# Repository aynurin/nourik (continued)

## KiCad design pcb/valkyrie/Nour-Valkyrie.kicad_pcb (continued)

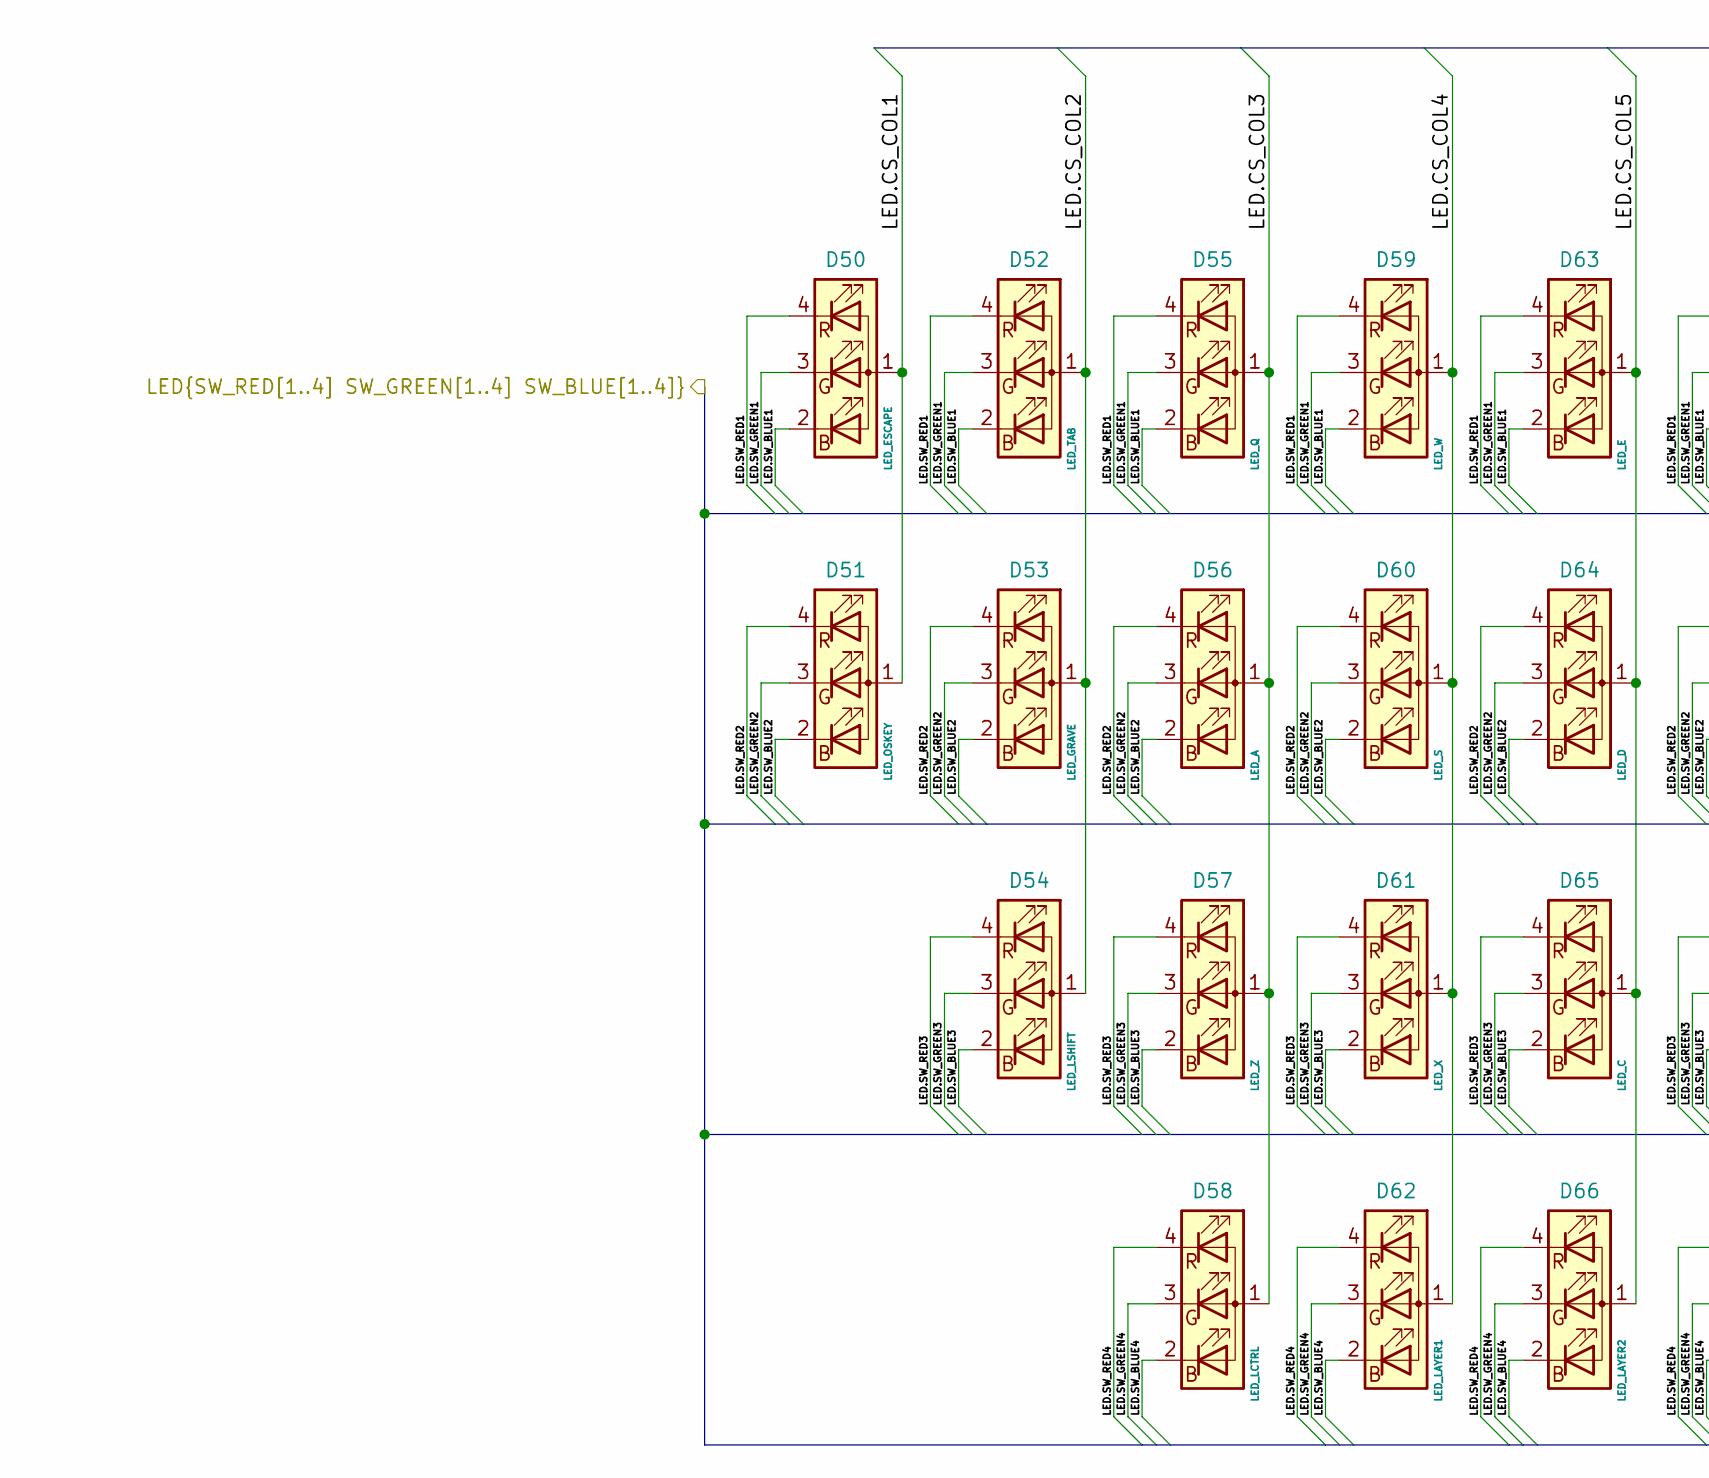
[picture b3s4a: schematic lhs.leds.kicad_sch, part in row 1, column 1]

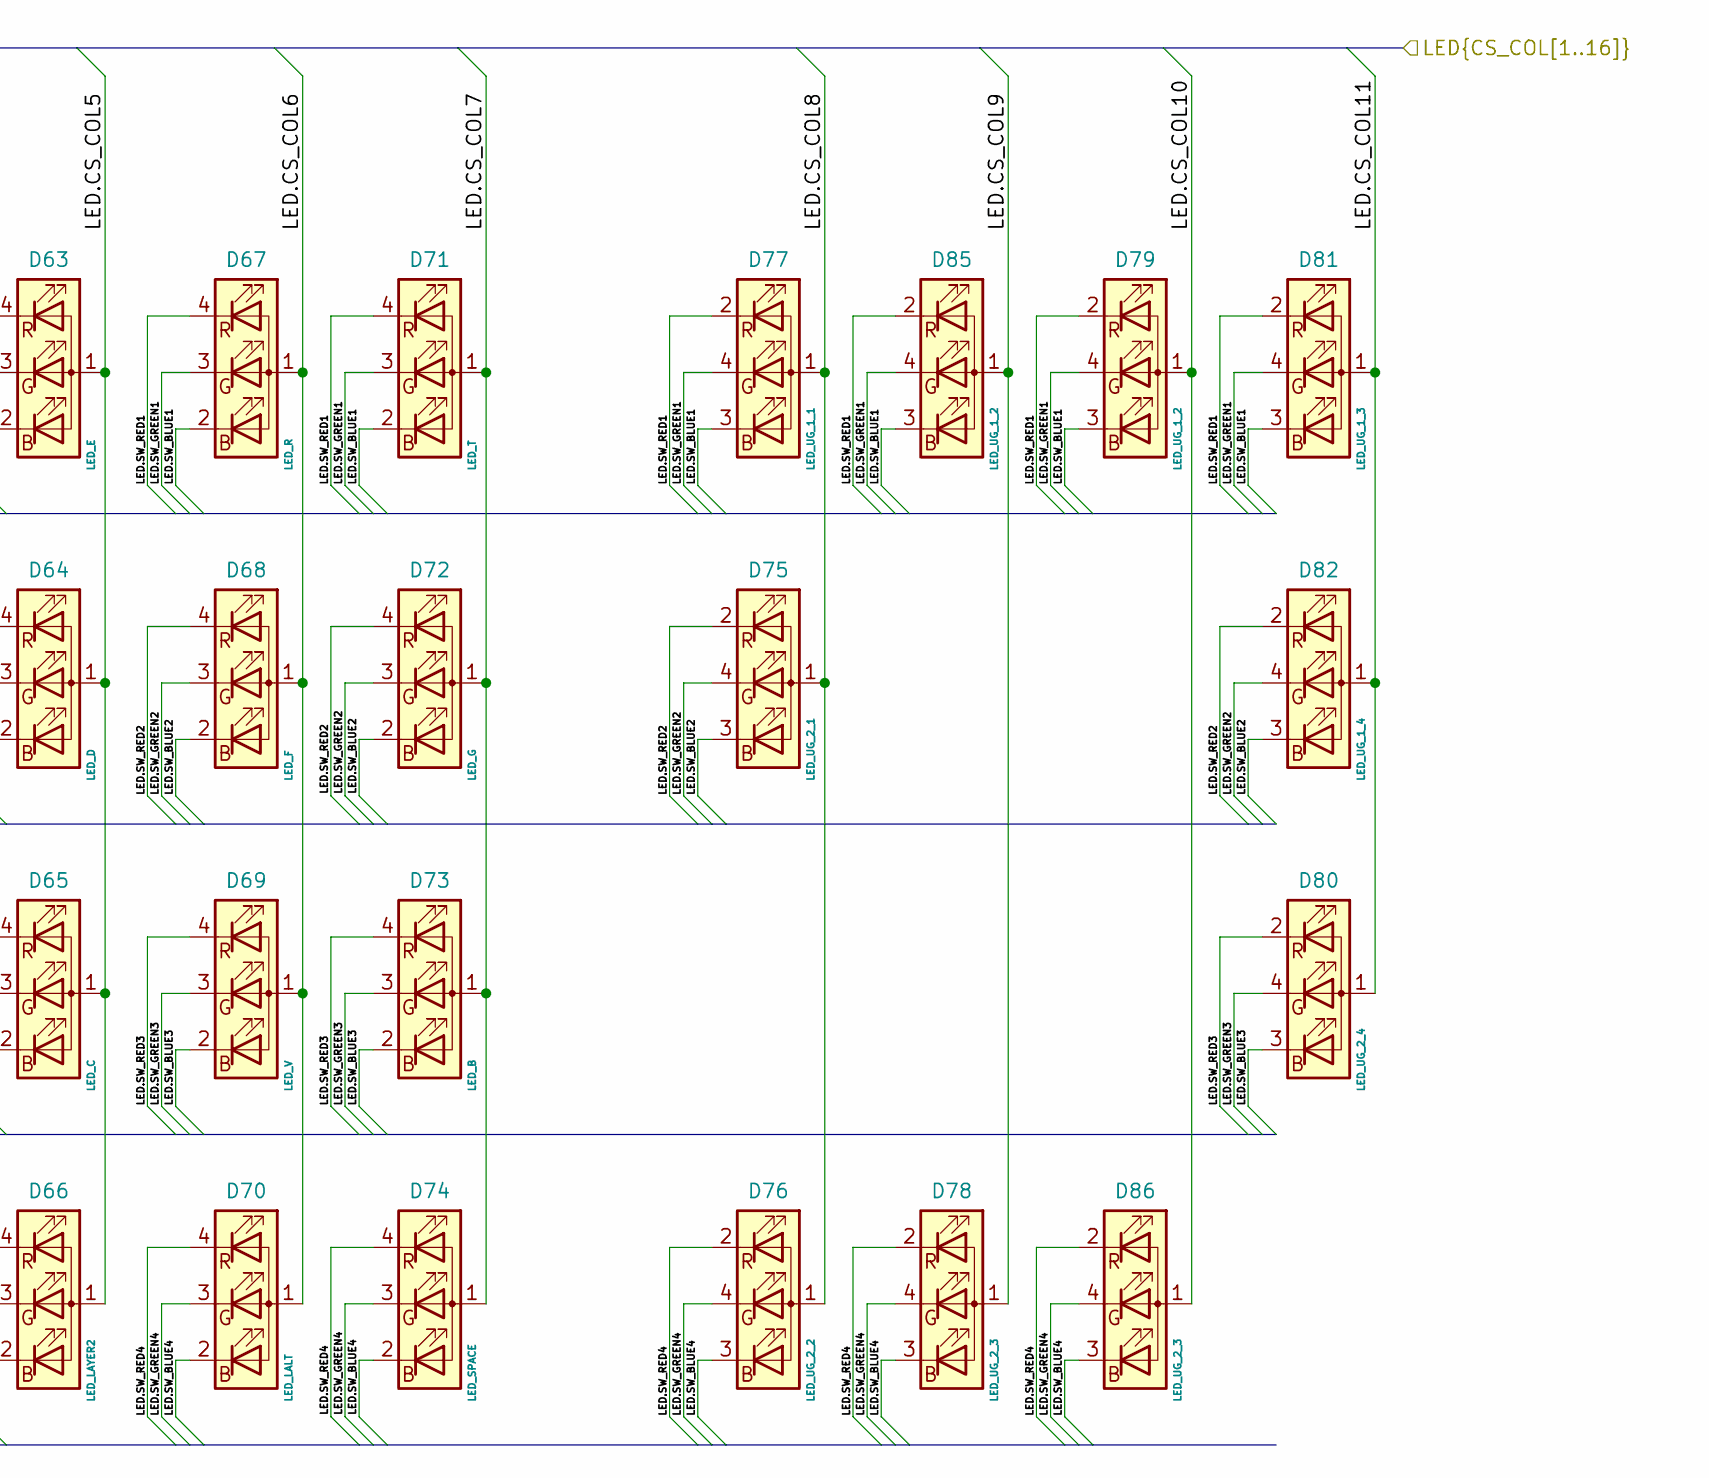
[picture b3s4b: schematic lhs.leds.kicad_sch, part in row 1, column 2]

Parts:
D50: LED_ESCAPE; 155124M173200
D51: LED_OSKEY; 155124M173200
D52: LED_TAB; 155124M173200
D53: LED_GRAVE; 155124M173200
D54: LED_LSHIFT; 155124M173200
D55: LED_Q; 155124M173200
D56: LED_A; 155124M173200
D57: LED_Z; 155124M173200
D58: LED_LCTRL; 155124M173200
D59: LED_W; 155124M173200
D60: LED_S; 155124M173200
D61: LED_X; 155124M173200
D62: LED_LAYER1; 155124M173200
D63: LED_E; 155124M173200
D64: LED_D; 155124M173200
D65: LED_C; 155124M173200
D66: LED_LAYER2; 155124M173200
D67: LED_R; 155124M173200
D68: LED_F; 155124M173200
D69: LED_V; 155124M173200
D70: LED_LALT; 155124M173200
D71: LED_T; 155124M173200
D72: LED_G; 155124M173200
D73: LED_B; 155124M173200
D74: LED_SPACE; 155124M173200
D75: LED_UG_2_1; LTRBR37G4R4S012502R18
D76: LED_UG_2_2; LTRBR37G4R4S012502R18
D77: LED_UG_1_1; LTRBR37G4R4S012502R18
D78, D86: LED_UG_2_3; LTRBR37G4R4S012502R18
D79, D85: LED_UG_1_2; LTRBR37G4R4S012502R18
D80: LED_UG_2_4; LTRBR37G4R4S012502R18
D81: LED_UG_1_3; LTRBR37G4R4S012502R18
D82: LED_UG_1_4; LTRBR37G4R4S012502R18

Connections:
/lhs/LHS LEDs/LED.CS_COL1: D50.1 (A), D51.1 (A); also elsewhere on the board
/lhs/LHS LEDs/LED.CS_COL2: D52.1 (A), D53.1 (A), D54.1 (A); also elsewhere on the board
/lhs/LHS LEDs/LED.CS_COL3: D55.1 (A), D56.1 (A), D57.1 (A), D58.1 (A); also elsewhere on the board
/lhs/LHS LEDs/LED.CS_COL4: D59.1 (A), D60.1 (A), D61.1 (A), D62.1 (A); also elsewhere on the board
/lhs/LHS LEDs/LED.CS_COL5: D63.1 (A), D64.1 (A), D65.1 (A), D66.1 (A); also elsewhere on the board
/lhs/LHS LEDs/LED.CS_COL6: D67.1 (A), D68.1 (A), D69.1 (A), D70.1 (A); also elsewhere on the board
/lhs/LHS LEDs/LED.CS_COL7: D71.1 (A), D72.1 (A), D73.1 (A), D74.1 (A); also elsewhere on the board
/lhs/LHS LEDs/LED.CS_COL8: D75.1 (A), D76.1 (A), D77.1 (A); also elsewhere on the board
/lhs/LHS LEDs/LED.CS_COL9: D78.1 (A), D85.1 (A); also elsewhere on the board
/lhs/LHS LEDs/LED.CS_COL10: D79.1 (A), D86.1 (A); also elsewhere on the board
/lhs/LHS LEDs/LED.CS_COL11: D80.1 (A), D81.1 (A), D82.1 (A); also elsewhere on the board
/lhs/LHS LEDs/LED.SW_BLUE1: D50.2 (BK), D52.2 (BK), D55.2 (BK), D59.2 (BK), D63.2 (BK), D67.2 (BK), D71.2 (BK), D77.3 (BK), D79.3 (BK), D81.3 (BK), D85.3 (BK); also elsewhere on the board
/lhs/LHS LEDs/LED.SW_BLUE2: D51.2 (BK), D53.2 (BK), D56.2 (BK), D60.2 (BK), D64.2 (BK), D68.2 (BK), D72.2 (BK), D75.3 (BK), D82.3 (BK); also elsewhere on the board
/lhs/LHS LEDs/LED.SW_BLUE3: D54.2 (BK), D57.2 (BK), D61.2 (BK), D65.2 (BK), D69.2 (BK), D73.2 (BK), D80.3 (BK); also elsewhere on the board
/lhs/LHS LEDs/LED.SW_BLUE4: D58.2 (BK), D62.2 (BK), D66.2 (BK), D70.2 (BK), D74.2 (BK), D76.3 (BK), D78.3 (BK), D86.3 (BK); also elsewhere on the board
/lhs/LHS LEDs/LED.SW_GREEN1: D50.3 (GK), D52.3 (GK), D55.3 (GK), D59.3 (GK), D63.3 (GK), D67.3 (GK), D71.3 (GK), D77.4 (GK), D79.4 (GK), D81.4 (GK), D85.4 (GK); also elsewhere on the board
/lhs/LHS LEDs/LED.SW_GREEN2: D51.3 (GK), D53.3 (GK), D56.3 (GK), D60.3 (GK), D64.3 (GK), D68.3 (GK), D72.3 (GK), D75.4 (GK), D82.4 (GK); also elsewhere on the board
/lhs/LHS LEDs/LED.SW_GREEN3: D54.3 (GK), D57.3 (GK), D61.3 (GK), D65.3 (GK), D69.3 (GK), D73.3 (GK), D80.4 (GK); also elsewhere on the board
/lhs/LHS LEDs/LED.SW_GREEN4: D58.3 (GK), D62.3 (GK), D66.3 (GK), D70.3 (GK), D74.3 (GK), D76.4 (GK), D78.4 (GK), D86.4 (GK); also elsewhere on the board
/lhs/LHS LEDs/LED.SW_RED1: D50.4 (RK), D52.4 (RK), D55.4 (RK), D59.4 (RK), D63.4 (RK), D67.4 (RK), D71.4 (RK), D77.2 (RK), D79.2 (RK), D81.2 (RK), D85.2 (RK); also elsewhere on the board
/lhs/LHS LEDs/LED.SW_RED2: D51.4 (RK), D53.4 (RK), D56.4 (RK), D60.4 (RK), D64.4 (RK), D68.4 (RK), D72.4 (RK), D75.2 (RK), D82.2 (RK); also elsewhere on the board
/lhs/LHS LEDs/LED.SW_RED3: D54.4 (RK), D57.4 (RK), D61.4 (RK), D65.4 (RK), D69.4 (RK), D73.4 (RK), D80.2 (RK); also elsewhere on the board
/lhs/LHS LEDs/LED.SW_RED4: D58.4 (RK), D62.4 (RK), D66.4 (RK), D70.4 (RK), D74.4 (RK), D76.2 (RK), D78.2 (RK), D86.2 (RK); also elsewhere on the board

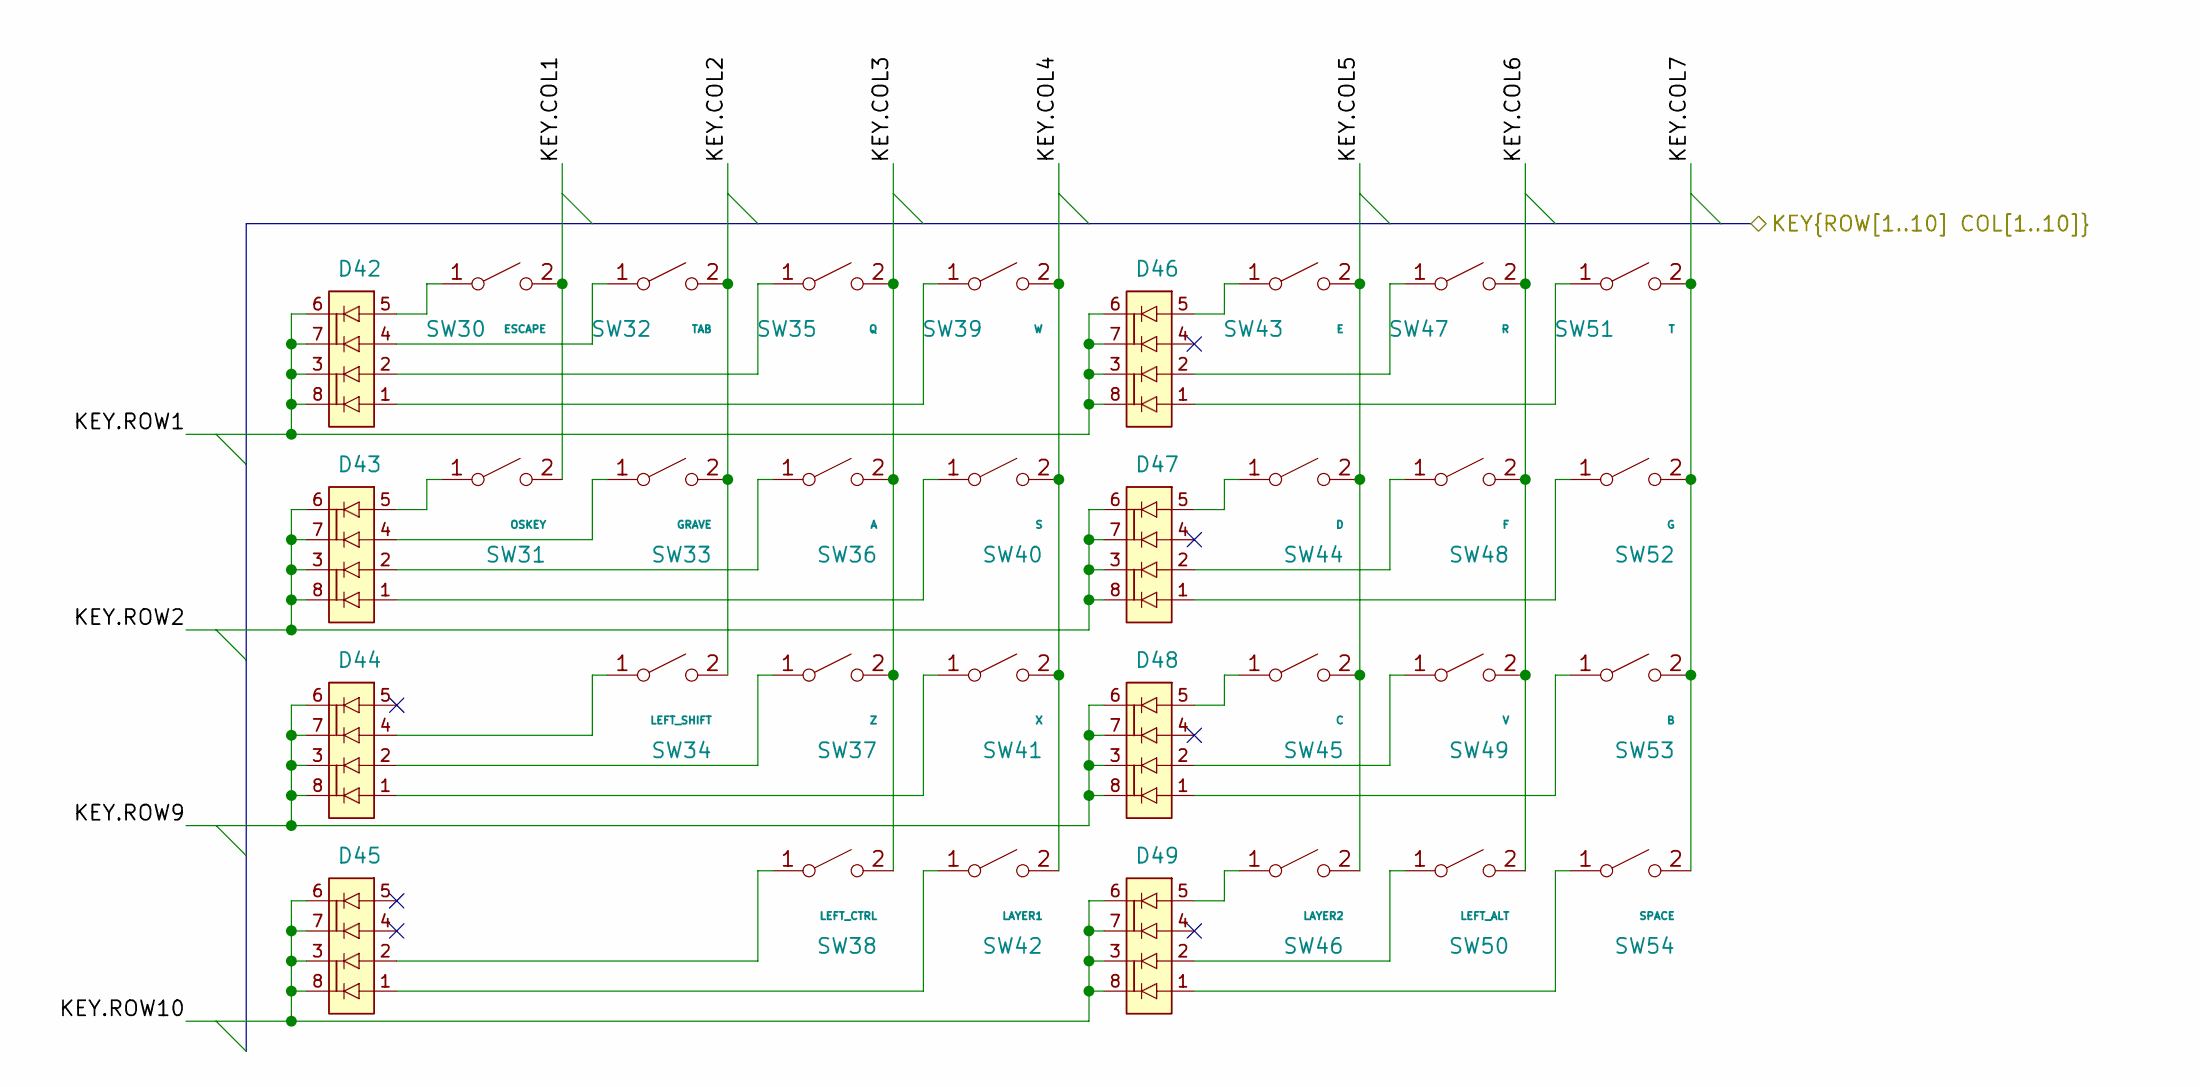
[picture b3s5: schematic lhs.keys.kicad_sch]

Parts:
D42, D43, D44, D45, D46, D47, D48, D49: BAV70SRAZ; DIO_BAV70SRAZ; PARTREV v.2
SW30: ESCAPE; MX_Choc_1U
SW31: OSKEY; MX_Choc_1U
SW32: TAB; MX_Choc_1U
SW33: GRAVE; MX_Choc_1U
SW34: LEFT_SHIFT; MX_Choc_1U
SW35: Q; MX_Choc_1U
SW36: A; MX_Choc_1U
SW37: Z; MX_Choc_1U
SW38: LEFT_CTRL; MX_Choc_1U
SW39: W; MX_Choc_1U
SW40: S; MX_Choc_1U
SW41: X; MX_Choc_1U
SW42: LAYER1; MX_Choc_1U
SW43: E; MX_Choc_1U
SW44: D; MX_Choc_1U
SW45: C; MX_Choc_1U
SW46: LAYER2; MX_Choc_1U
SW47: R; MX_Choc_1U
SW48: F; MX_Choc_1U
SW49: V; MX_Choc_1U
SW50: LEFT_ALT; MX_Choc_1U
SW51: T; MX_Choc_1U
SW52: G; MX_Choc_1U
SW53: B; MX_Choc_1U
SW54: SPACE; MX_Choc_1U

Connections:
/lhs/LHS Keys/KEY.COL1: SW30.2 (B), SW31.2 (B); also elsewhere on the board
/lhs/LHS Keys/KEY.COL2: SW32.2 (B), SW33.2 (B), SW34.2 (B); also elsewhere on the board
/lhs/LHS Keys/KEY.COL3: SW35.2 (B), SW36.2 (B), SW37.2 (B), SW38.2 (B); also elsewhere on the board
/lhs/LHS Keys/KEY.COL4: SW39.2 (B), SW40.2 (B), SW41.2 (B), SW42.2 (B); also elsewhere on the board
/lhs/LHS Keys/KEY.COL5: SW43.2 (B), SW44.2 (B), SW45.2 (B), SW46.2 (B); also elsewhere on the board
/lhs/LHS Keys/KEY.COL6: SW47.2 (B), SW48.2 (B), SW49.2 (B), SW50.2 (B); also elsewhere on the board
/lhs/LHS Keys/KEY.COL7: SW51.2 (B), SW52.2 (B), SW53.2 (B), SW54.2 (B); also elsewhere on the board
/lhs/LHS Keys/KEY.ROW1: D42.3, D42.6, D42.7, D42.8, D46.3, D46.6, D46.7, D46.8; also elsewhere on the board
/lhs/LHS Keys/KEY.ROW2: D43.3, D43.6, D43.7, D43.8, D47.3, D47.6, D47.7, D47.8; also elsewhere on the board
/lhs/LHS Keys/KEY.ROW9: D44.3, D44.6, D44.7, D44.8, D48.3, D48.6, D48.7, D48.8; also elsewhere on the board
/lhs/LHS Keys/KEY.ROW10: D45.3, D45.6, D45.7, D45.8, D49.3, D49.6, D49.7, D49.8; also elsewhere on the board
unnamed: D42.1, SW39.1 (A)
unnamed: D42.2, SW35.1 (A)
unnamed: D42.4, SW32.1 (A)
unnamed: D42.5, SW30.1 (A)
unnamed: D43.1, SW40.1 (A)
unnamed: D43.2, SW36.1 (A)
unnamed: D43.4, SW33.1 (A)
unnamed: D43.5, SW31.1 (A)
unnamed: D44.1, SW41.1 (A)
unnamed: D44.2, SW37.1 (A)
unnamed: D44.4, SW34.1 (A)
unnamed: D45.1, SW42.1 (A)
unnamed: D45.2, SW38.1 (A)
unnamed: D46.1, SW51.1 (A)
unnamed: D46.2, SW47.1 (A)
unnamed: D46.5, SW43.1 (A)
unnamed: D47.1, SW52.1 (A)
unnamed: D47.2, SW48.1 (A)
unnamed: D47.5, SW44.1 (A)
unnamed: D48.1, SW53.1 (A)
unnamed: D48.2, SW49.1 (A)
unnamed: D48.5, SW45.1 (A)
unnamed: D49.1, SW54.1 (A)
unnamed: D49.2, SW50.1 (A)
unnamed: D49.5, SW46.1 (A)

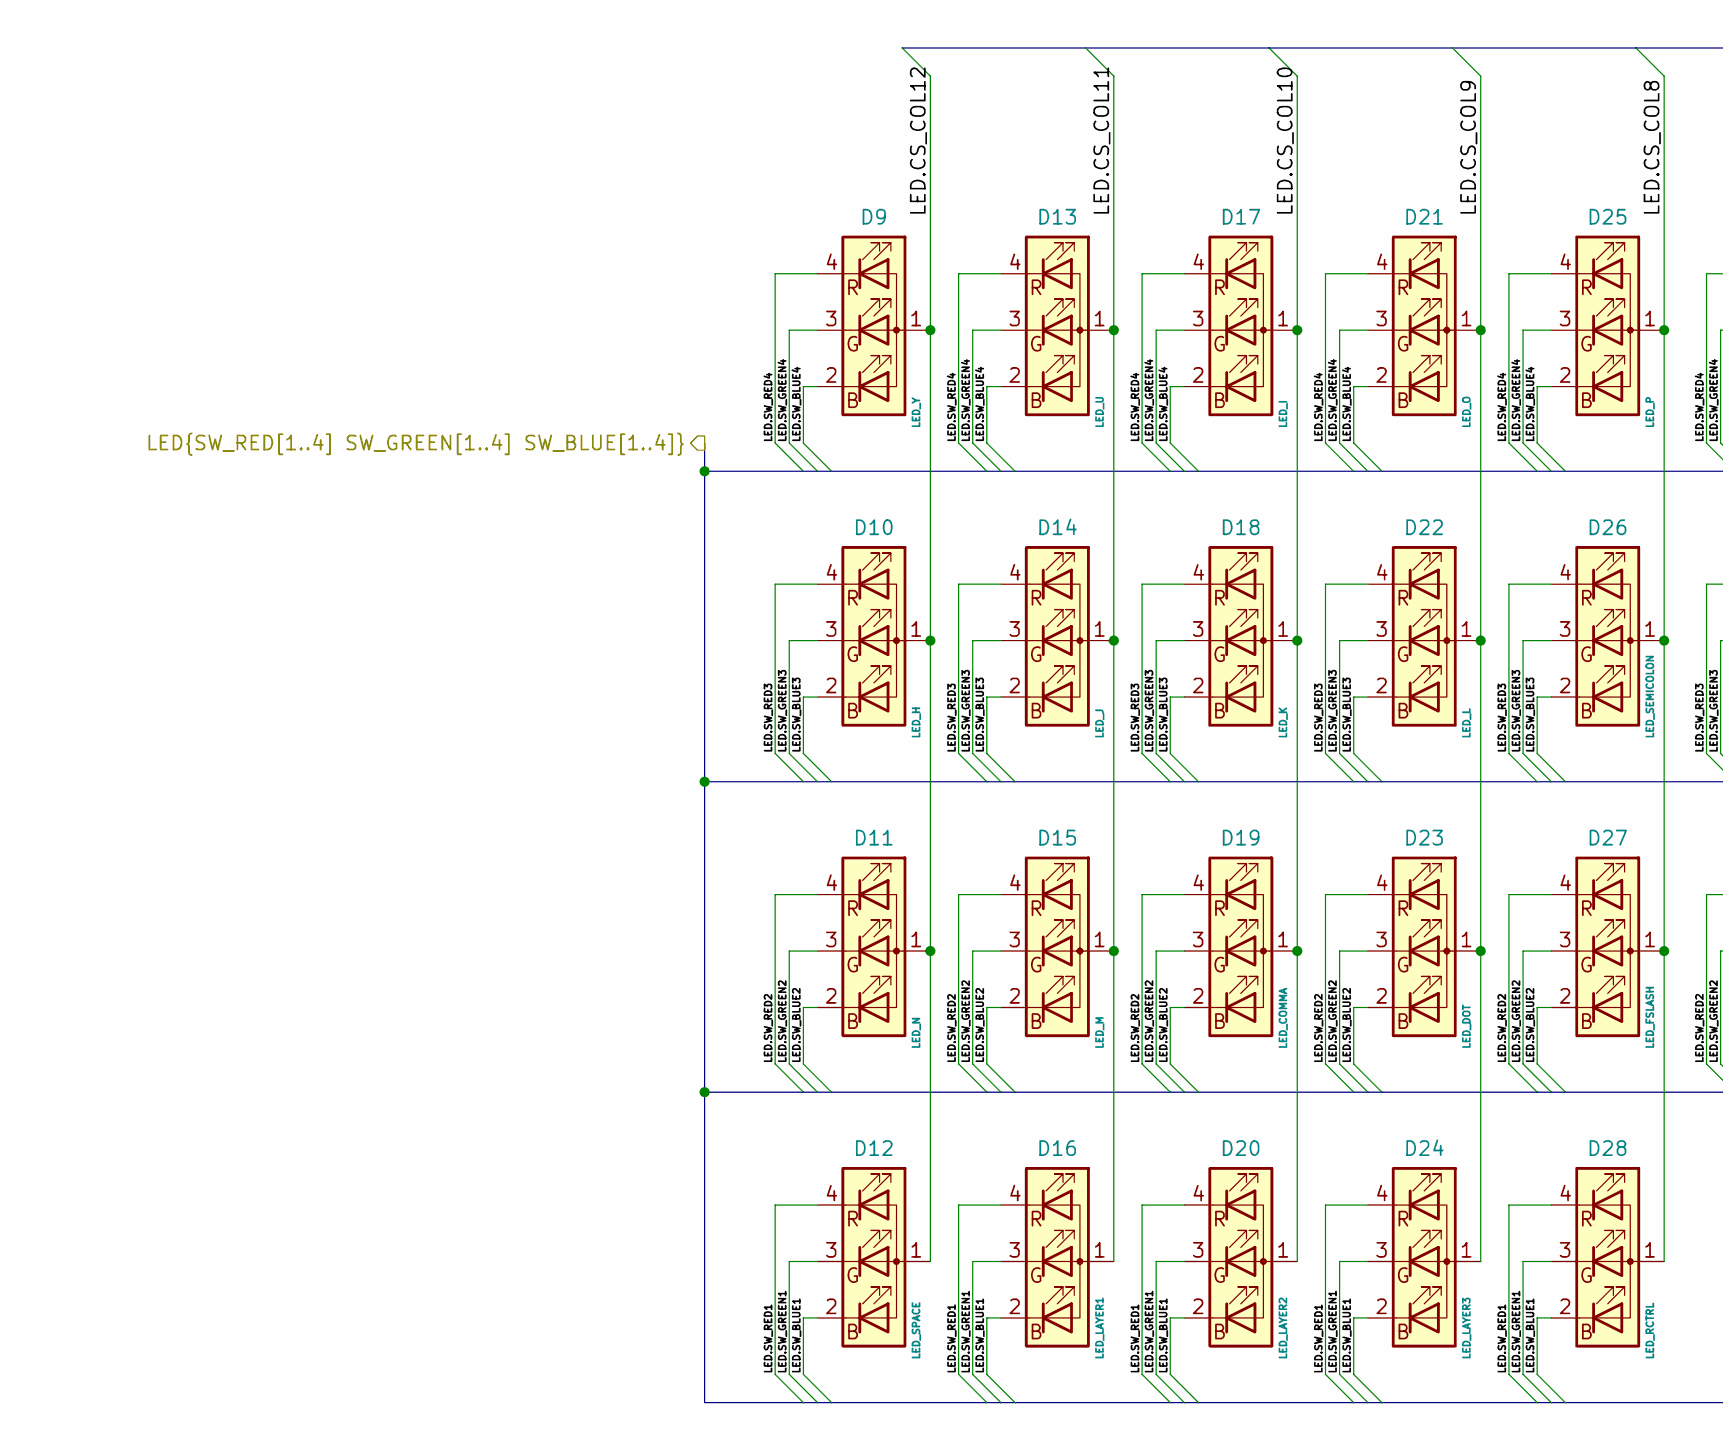
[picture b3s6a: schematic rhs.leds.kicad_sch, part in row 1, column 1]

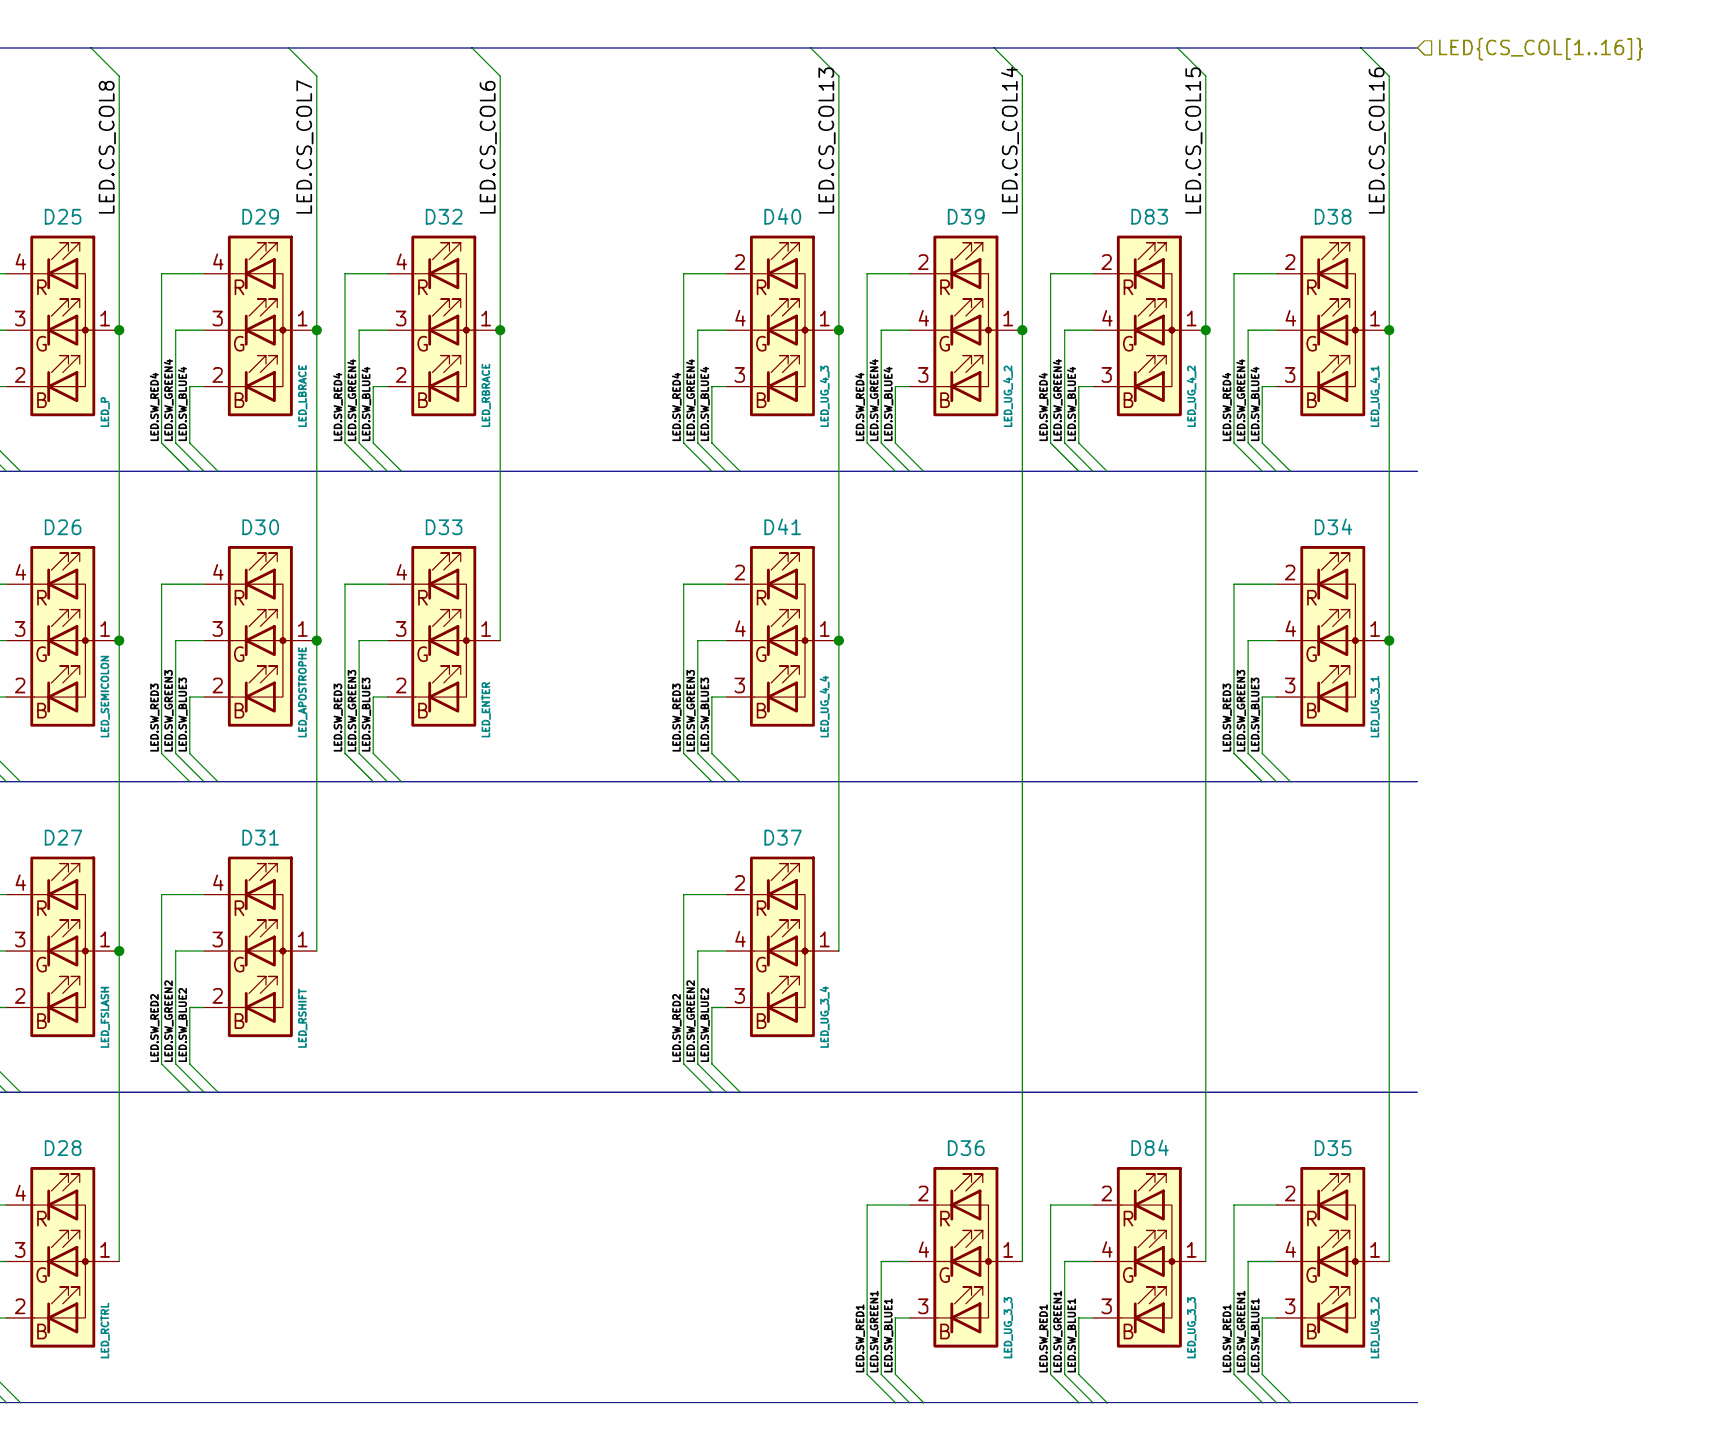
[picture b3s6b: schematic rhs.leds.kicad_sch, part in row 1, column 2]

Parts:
D9: LED_Y; 155124M173200
D10: LED_H; 155124M173200
D11: LED_N; 155124M173200
D12: LED_SPACE; 155124M173200
D13: LED_U; 155124M173200
D14: LED_J; 155124M173200
D15: LED_M; 155124M173200
D16: LED_LAYER1; 155124M173200
D17: LED_I; 155124M173200
D18: LED_K; 155124M173200
D19: LED_COMMA; 155124M173200
D20: LED_LAYER2; 155124M173200
D21: LED_O; 155124M173200
D22: LED_L; 155124M173200
D23: LED_DOT; 155124M173200
D24: LED_LAYER3; 155124M173200
D25: LED_P; 155124M173200
D26: LED_SEMICOLON; 155124M173200
D27: LED_FSLASH; 155124M173200
D28: LED_RCTRL; 155124M173200
D29: LED_LBRACE; 155124M173200
D30: LED_APOSTROPHE; 155124M173200
D31: LED_RSHIFT; 155124M173200
D32: LED_RBRACE; 155124M173200
D33: LED_ENTER; 155124M173200
D34: LED_UG_3_1; LTRBR37G4R4S012502R18
D35: LED_UG_3_2; LTRBR37G4R4S012502R18
D36, D84: LED_UG_3_3; LTRBR37G4R4S012502R18
D37: LED_UG_3_4; LTRBR37G4R4S012502R18
D38: LED_UG_4_1; LTRBR37G4R4S012502R18
D39, D83: LED_UG_4_2; LTRBR37G4R4S012502R18
D40: LED_UG_4_3; LTRBR37G4R4S012502R18
D41: LED_UG_4_4; LTRBR37G4R4S012502R18

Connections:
/rhs/RHS LEDs/LED.CS_COL6: D32.1 (A), D33.1 (A); also elsewhere on the board
/rhs/RHS LEDs/LED.CS_COL7: D29.1 (A), D30.1 (A), D31.1 (A); also elsewhere on the board
/rhs/RHS LEDs/LED.CS_COL8: D25.1 (A), D26.1 (A), D27.1 (A), D28.1 (A); also elsewhere on the board
/rhs/RHS LEDs/LED.CS_COL9: D21.1 (A), D22.1 (A), D23.1 (A), D24.1 (A); also elsewhere on the board
/rhs/RHS LEDs/LED.CS_COL10: D17.1 (A), D18.1 (A), D19.1 (A), D20.1 (A); also elsewhere on the board
/rhs/RHS LEDs/LED.CS_COL11: D13.1 (A), D14.1 (A), D15.1 (A), D16.1 (A); also elsewhere on the board
/rhs/RHS LEDs/LED.CS_COL12: D9.1 (A), D10.1 (A), D11.1 (A), D12.1 (A); also elsewhere on the board
/rhs/RHS LEDs/LED.CS_COL13: D37.1 (A), D40.1 (A), D41.1 (A); also elsewhere on the board
/rhs/RHS LEDs/LED.CS_COL14: D36.1 (A), D39.1 (A); also elsewhere on the board
/rhs/RHS LEDs/LED.CS_COL15: D83.1 (A), D84.1 (A); also elsewhere on the board
/rhs/RHS LEDs/LED.CS_COL16: D34.1 (A), D35.1 (A), D38.1 (A); also elsewhere on the board
/rhs/RHS LEDs/LED.SW_BLUE1: D12.2 (BK), D16.2 (BK), D20.2 (BK), D24.2 (BK), D28.2 (BK), D35.3 (BK), D36.3 (BK), D84.3 (BK); also elsewhere on the board
/rhs/RHS LEDs/LED.SW_BLUE2: D11.2 (BK), D15.2 (BK), D19.2 (BK), D23.2 (BK), D27.2 (BK), D31.2 (BK), D37.3 (BK); also elsewhere on the board
/rhs/RHS LEDs/LED.SW_BLUE3: D10.2 (BK), D14.2 (BK), D18.2 (BK), D22.2 (BK), D26.2 (BK), D30.2 (BK), D33.2 (BK), D34.3 (BK), D41.3 (BK); also elsewhere on the board
/rhs/RHS LEDs/LED.SW_BLUE4: D9.2 (BK), D13.2 (BK), D17.2 (BK), D21.2 (BK), D25.2 (BK), D29.2 (BK), D32.2 (BK), D38.3 (BK), D39.3 (BK), D40.3 (BK), D83.3 (BK); also elsewhere on the board
/rhs/RHS LEDs/LED.SW_GREEN1: D12.3 (GK), D16.3 (GK), D20.3 (GK), D24.3 (GK), D28.3 (GK), D35.4 (GK), D36.4 (GK), D84.4 (GK); also elsewhere on the board
/rhs/RHS LEDs/LED.SW_GREEN2: D11.3 (GK), D15.3 (GK), D19.3 (GK), D23.3 (GK), D27.3 (GK), D31.3 (GK), D37.4 (GK); also elsewhere on the board
/rhs/RHS LEDs/LED.SW_GREEN3: D10.3 (GK), D14.3 (GK), D18.3 (GK), D22.3 (GK), D26.3 (GK), D30.3 (GK), D33.3 (GK), D34.4 (GK), D41.4 (GK); also elsewhere on the board
/rhs/RHS LEDs/LED.SW_GREEN4: D9.3 (GK), D13.3 (GK), D17.3 (GK), D21.3 (GK), D25.3 (GK), D29.3 (GK), D32.3 (GK), D38.4 (GK), D39.4 (GK), D40.4 (GK), D83.4 (GK); also elsewhere on the board
/rhs/RHS LEDs/LED.SW_RED1: D12.4 (RK), D16.4 (RK), D20.4 (RK), D24.4 (RK), D28.4 (RK), D35.2 (RK), D36.2 (RK), D84.2 (RK); also elsewhere on the board
/rhs/RHS LEDs/LED.SW_RED2: D11.4 (RK), D15.4 (RK), D19.4 (RK), D23.4 (RK), D27.4 (RK), D31.4 (RK), D37.2 (RK); also elsewhere on the board
/rhs/RHS LEDs/LED.SW_RED3: D10.4 (RK), D14.4 (RK), D18.4 (RK), D22.4 (RK), D26.4 (RK), D30.4 (RK), D33.4 (RK), D34.2 (RK), D41.2 (RK); also elsewhere on the board
/rhs/RHS LEDs/LED.SW_RED4: D9.4 (RK), D13.4 (RK), D17.4 (RK), D21.4 (RK), D25.4 (RK), D29.4 (RK), D32.4 (RK), D38.2 (RK), D39.2 (RK), D40.2 (RK), D83.2 (RK); also elsewhere on the board

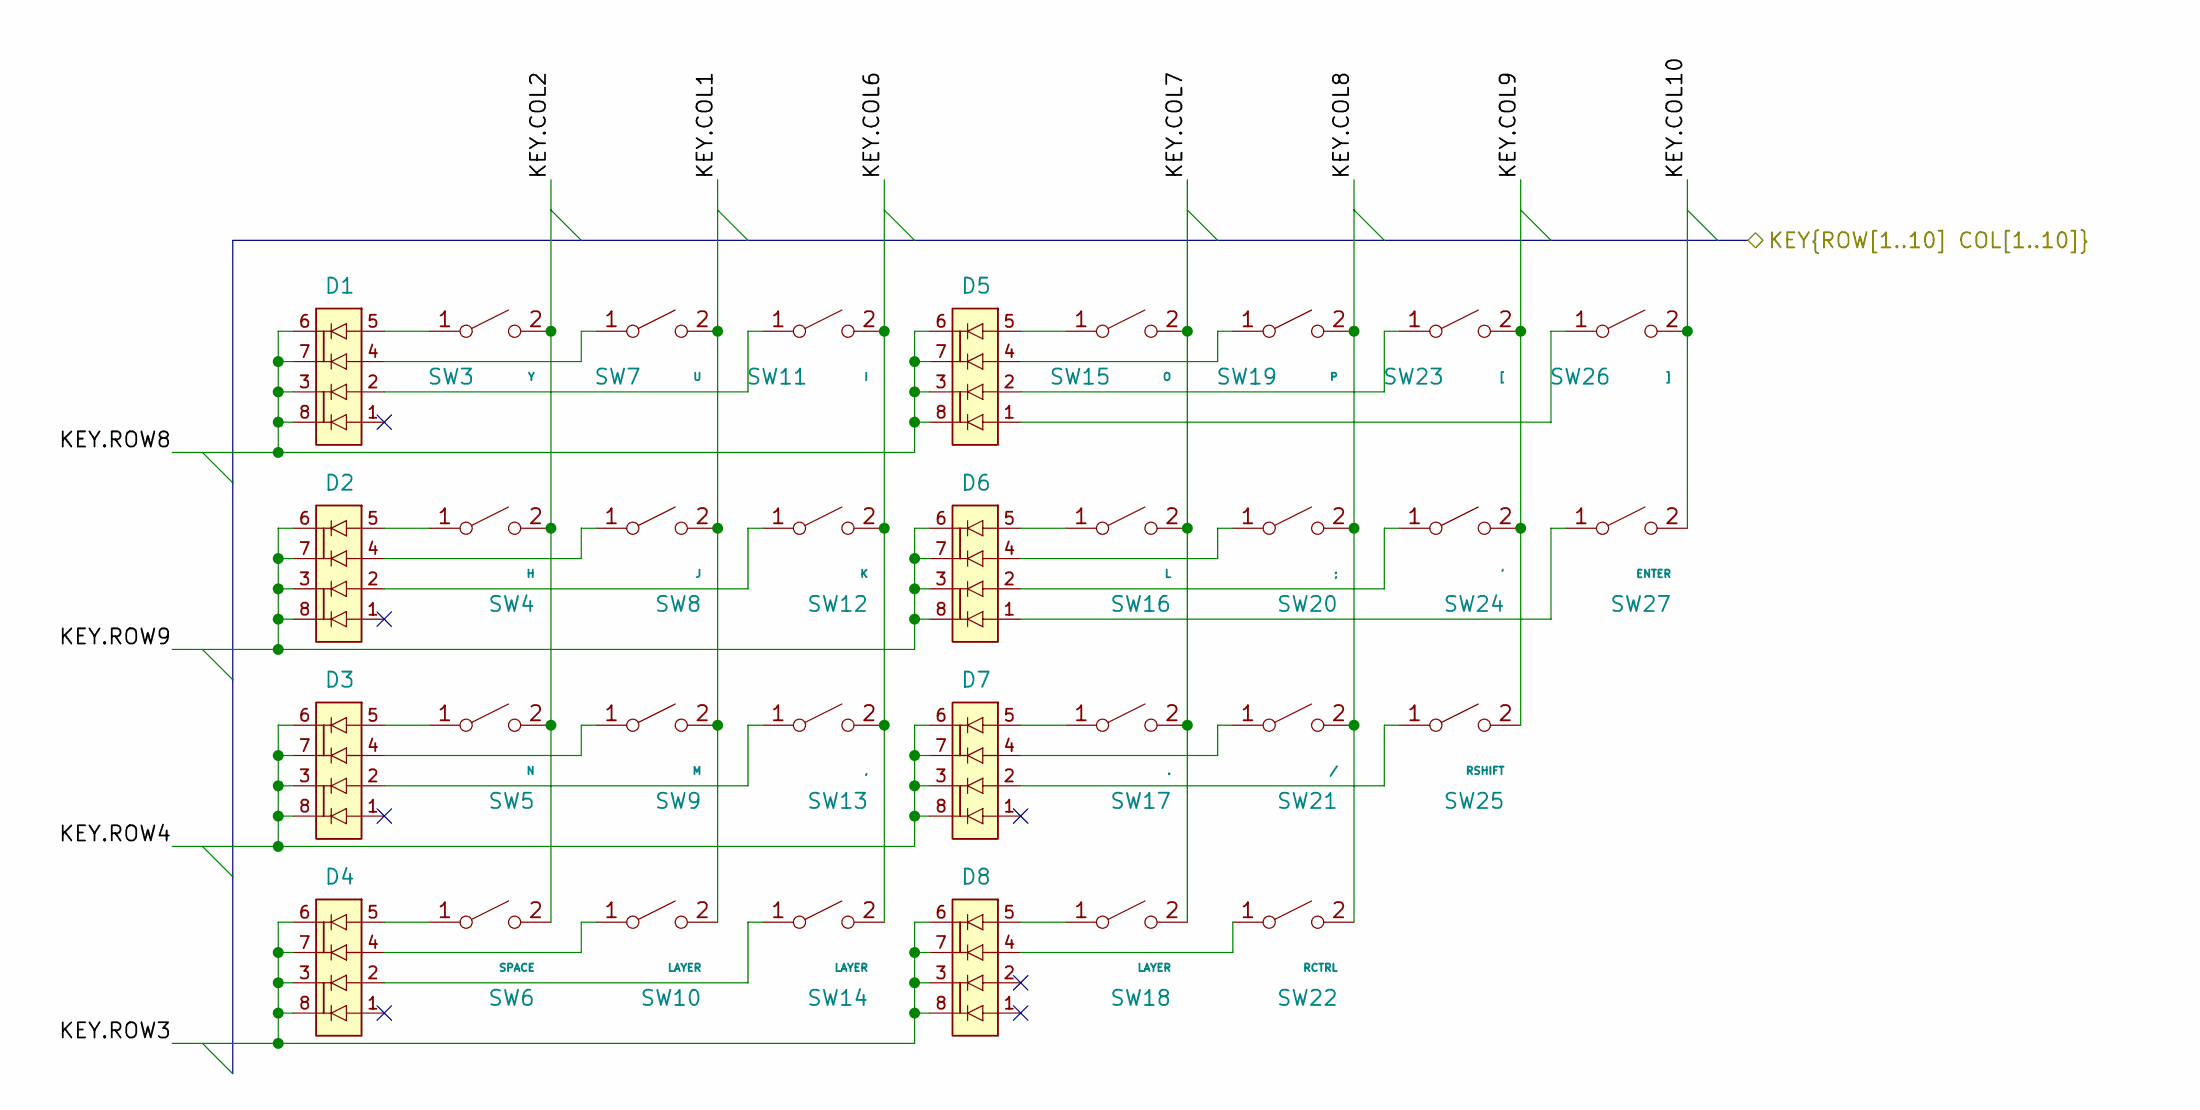
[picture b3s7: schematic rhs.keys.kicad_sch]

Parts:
D1, D2, D3, D4, D5, D6, D7, D8: BAV70SRAZ; DIO_BAV70SRAZ; PARTREV v.2
SW3: Y; MX_Choc_1U
SW4: H; MX_Choc_1U
SW5: N; MX_Choc_1U
SW6: SPACE; MX_Choc_1U
SW7: U; MX_Choc_1U
SW8: J; MX_Choc_1U
SW9: M; MX_Choc_1U
SW10, SW14, SW18: LAYER; MX_Choc_1U
SW11: I; MX_Choc_1U
SW12: K; MX_Choc_1U
SW13: ,; MX_Choc_1U
SW15: O; MX_Choc_1U
SW16: L; MX_Choc_1U
SW17: .; MX_Choc_1U
SW19: P; MX_Choc_1U
SW20: ;; MX_Choc_1U
SW21: /; MX_Choc_1U
SW22: RCTRL; MX_Choc_1U
SW23: [; MX_Choc_1U
SW24: '; MX_Choc_1U
SW25: RSHIFT; MX_Choc_1U
SW26: ]; MX_Choc_1U
SW27: ENTER; MX_Choc_1U

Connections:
/rhs/RHS Keys/KEY.COL1: SW7.2 (B), SW8.2 (B), SW9.2 (B), SW10.2 (B); also elsewhere on the board
/rhs/RHS Keys/KEY.COL2: SW3.2 (B), SW4.2 (B), SW5.2 (B), SW6.2 (B); also elsewhere on the board
/rhs/RHS Keys/KEY.COL6: SW11.2 (B), SW12.2 (B), SW13.2 (B), SW14.2 (B); also elsewhere on the board
/rhs/RHS Keys/KEY.COL7: SW15.2 (B), SW16.2 (B), SW17.2 (B), SW18.2 (B); also elsewhere on the board
/rhs/RHS Keys/KEY.COL8: SW19.2 (B), SW20.2 (B), SW21.2 (B), SW22.2 (B); also elsewhere on the board
/rhs/RHS Keys/KEY.COL9: SW23.2 (B), SW24.2 (B), SW25.2 (B); also elsewhere on the board
/rhs/RHS Keys/KEY.COL10: SW26.2 (B), SW27.2 (B); also elsewhere on the board
/rhs/RHS Keys/KEY.ROW3: D4.3, D4.6, D4.7, D4.8, D8.3, D8.6, D8.7, D8.8; also elsewhere on the board
/rhs/RHS Keys/KEY.ROW4: D3.3, D3.6, D3.7, D3.8, D7.3, D7.6, D7.7, D7.8; also elsewhere on the board
/rhs/RHS Keys/KEY.ROW8: D1.3, D1.6, D1.7, D1.8, D5.3, D5.6, D5.7, D5.8; also elsewhere on the board
/rhs/RHS Keys/KEY.ROW9: D2.3, D2.6, D2.7, D2.8, D6.3, D6.6, D6.7, D6.8; also elsewhere on the board
unnamed: D1.2, SW11.1 (A)
unnamed: D1.4, SW7.1 (A)
unnamed: D1.5, SW3.1 (A)
unnamed: D2.2, SW12.1 (A)
unnamed: D2.4, SW8.1 (A)
unnamed: D2.5, SW4.1 (A)
unnamed: D3.2, SW13.1 (A)
unnamed: D3.4, SW9.1 (A)
unnamed: D3.5, SW5.1 (A)
unnamed: D4.2, SW14.1 (A)
unnamed: D4.4, SW10.1 (A)
unnamed: D4.5, SW6.1 (A)
unnamed: D5.1, SW26.1 (A)
unnamed: D5.2, SW23.1 (A)
unnamed: D5.4, SW19.1 (A)
unnamed: D5.5, SW15.1 (A)
unnamed: D6.1, SW27.1 (A)
unnamed: D6.2, SW24.1 (A)
unnamed: D6.4, SW20.1 (A)
unnamed: D6.5, SW16.1 (A)
unnamed: D7.2, SW25.1 (A)
unnamed: D7.4, SW21.1 (A)
unnamed: D7.5, SW17.1 (A)
unnamed: D8.4, SW22.1 (A)
unnamed: D8.5, SW18.1 (A)
